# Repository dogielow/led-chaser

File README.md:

# led-chaser
electronic led chaser

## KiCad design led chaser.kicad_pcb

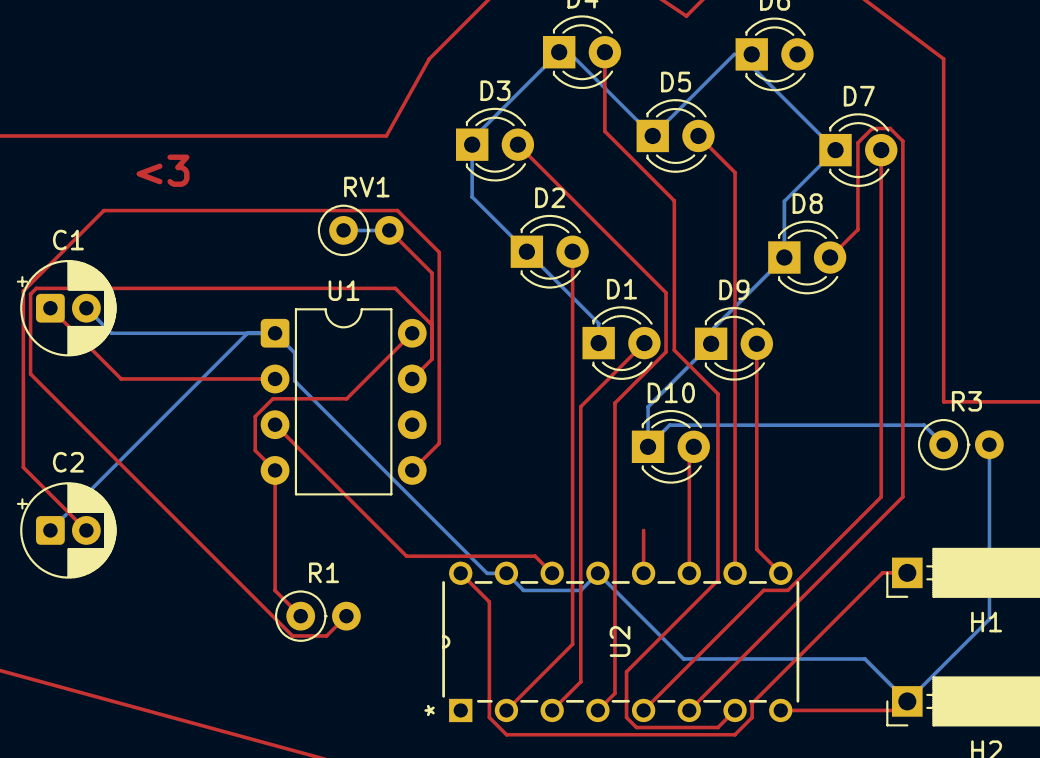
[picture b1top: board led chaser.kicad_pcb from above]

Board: 2 copper layers, 19 parts (0 on the bottom side), 17 nets.

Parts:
C1: 1uF; CP_Radial_D5.0mm_P2.00mm
C2: 0.01uF; CP_Radial_D5.0mm_P2.00mm
D1, D2, D3, D4, D5, D6, D7, D8, D9, D10: LED; LED_D3.0mm
H1, H2: MountingHole_Pad; PinSocket_1x01_P2.54mm_Horizontal
R1: 1k; R_Axial_DIN0207_L6.3mm_D2.5mm_P2.54mm_Vertical
R3: 330; R_Axial_DIN0207_L6.3mm_D2.5mm_P2.54mm_Vertical
RV1: 50k; R_Axial_DIN0207_L6.3mm_D2.5mm_P2.54mm_Vertical
U1: NE555P; DIP-8_W7.62mm
U2: 4017; N16

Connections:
+5V: H1.1, R1.1, U1.4 (~RST), U1.8 (VCC), U2.16 (VDD)
GND: C1.2, C2.1, H2.1, R3.2, U1.1 (GND), U2.8 (VSS), U2.13 (CKEN), U2.15 (Reset)
unnamed: D1.2 (A), U2.3 (Q0)
unnamed: D1.1 (K), D2.1 (K), D3.1 (K), D4.1 (K), D5.1 (K), D6.1 (K), D7.1 (K), D8.1 (K), D9.1 (K), D10.1 (K), R3.1
unnamed: D2.2 (A), U2.2 (Q1)
unnamed: D3.2 (A), U2.4 (Q2)
unnamed: D4.2 (A), U2.7 (Q3)
unnamed: D5.2 (A), U2.10 (Q4)
unnamed: D6.2 (A), U2.1 (Q5)
unnamed: D7.2 (A), U2.5 (Q6)
unnamed: D8.2 (A), U2.6 (Q7)
unnamed: D9.2 (A), U2.9 (Q8)
unnamed: D10.2 (A), U2.11 (Q9)
unnamed: C2.2, U1.5 (CONT)
unnamed: R1.2, RV1.1, RV1.2, U1.7 (DISCH)
OUT: U1.3 (OUT), U2.14 (CLK)
tr: C1.1, U1.2 (TRIG)
